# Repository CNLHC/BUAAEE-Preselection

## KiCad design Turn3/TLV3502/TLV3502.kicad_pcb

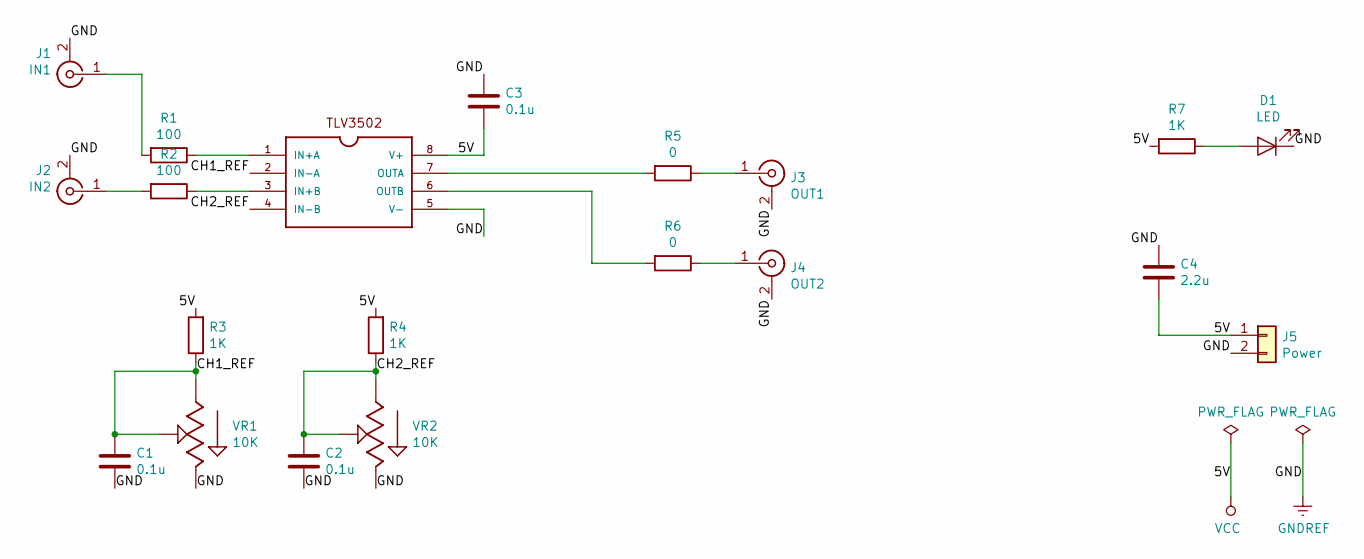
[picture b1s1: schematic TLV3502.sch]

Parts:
C1, C2, C3: 0.1u; C_0603_1608Metric_Pad1.05x0.95mm_HandSolder
C4: 2.2u; CP_EIA-3528-21_Kemet-B
D1: LED; LED_0805_2012Metric_Pad1.15x1.40mm_HandSolder
J1: IN1; SMA_Amphenol_132134_Vertical
J2: IN2; SMA_Amphenol_132134_Vertical
J3: OUT1; SMA_Amphenol_132134_Vertical
J4: OUT2; SMA_Amphenol_132134_Vertical
J5: Power; PinSocket_1x02_P2.54mm_Vertical
R1, R2: 100; R_0603_1608Metric_Pad1.05x0.95mm_HandSolder
R3, R4, R7: 1K; R_0603_1608Metric_Pad1.05x0.95mm_HandSolder
R5, R6: 0; R_0603_1608Metric_Pad1.05x0.95mm_HandSolder
U1: TLV3502; SOIC-8_3.9x4.9mm_P1.27mm
VR1, VR2: 10K; PinHeader_1x03_P2.54mm_Vertical

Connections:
/CH1_REF: C1.2, R3.1, U1.2 (IN-A), VR1.1 (CCW), VR1.2 (WIPER)
/CH2_REF: C2.2, R4.1, U1.4 (IN-B), VR2.1 (CCW), VR2.2 (WIPER)
GNDREF: C1.1, C2.1, C3.2, C4.2, D1.1 (K), J1.2 (Ext), J2.2 (Ext), J3.2 (Ext), J4.2 (Ext), J5.2, U1.5 (V-), VR1.3 (CW), VR2.3 (CW)
unnamed: D1.2 (A), R7.1
unnamed: J1.1 (In), R1.2
unnamed: J2.1 (In), R2.2
unnamed: J3.1 (In), R5.1
unnamed: J4.1 (In), R6.1
unnamed: R1.1, U1.1 (IN+A)
unnamed: R2.1, U1.3 (IN+B)
unnamed: R5.2, U1.7 (OUTA)
unnamed: R6.2, U1.6 (OUTB)
VCC: C3.1, C4.1, J5.1, R3.2, R4.2, R7.2, U1.8 (V+)

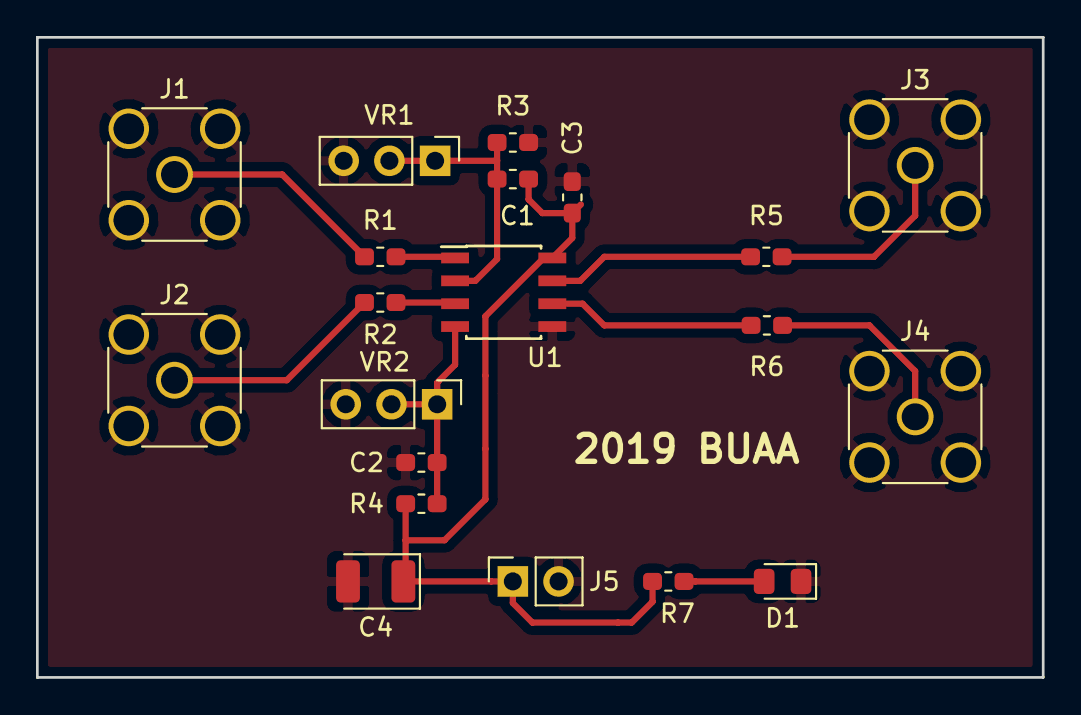
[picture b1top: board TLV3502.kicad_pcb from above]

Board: 2 copper layers, 55.9 x 35.6 mm, 20 parts (0 on the bottom side), 13 nets.

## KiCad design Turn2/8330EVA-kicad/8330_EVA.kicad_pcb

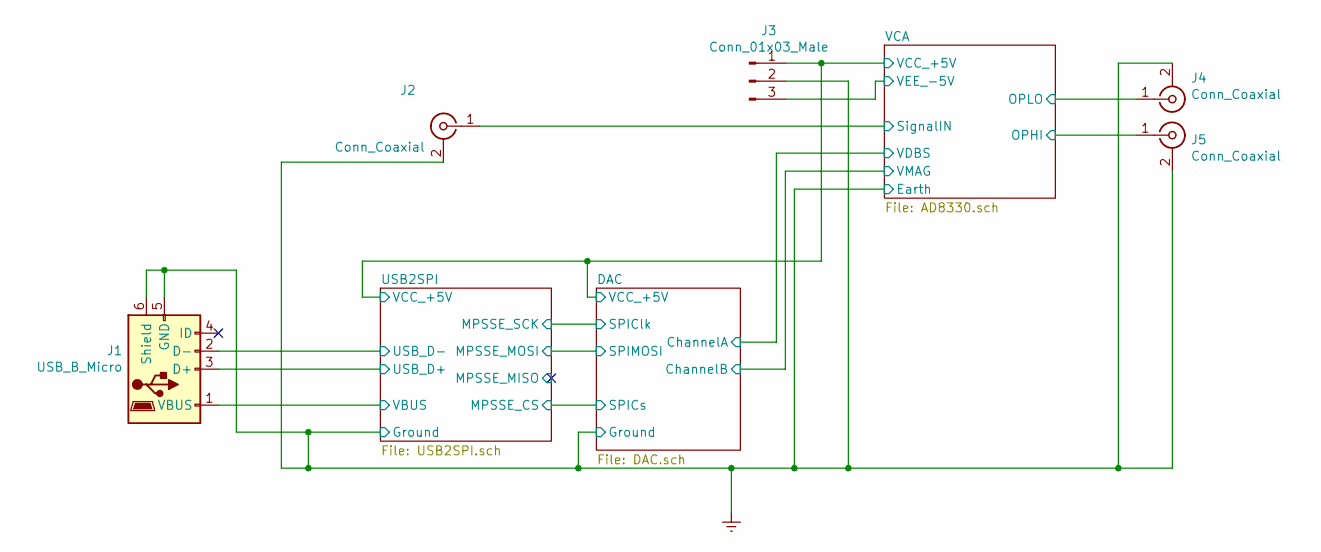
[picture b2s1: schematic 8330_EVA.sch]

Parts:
J1: USB_B_Micro; USB_Mini-B_Lumberg_2486_01_Horizontal
J2, J4, J5: Conn_Coaxial; SMA_Amphenol_132289_EdgeMount
J3: Conn_01x03_Male; PinHeader_1x03_P2.54mm_Vertical

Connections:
/DAC/VCC_+5V: J3.1; also elsewhere on the board
/USB2SPI/USB_D+: J1.3 (D+); also elsewhere on the board
/USB2SPI/USB_D-: J1.2 (D-); also elsewhere on the board
/USB2SPI/VBUS: J1.1 (VBUS); also elsewhere on the board
/VCA/OPHI: J5.1 (In); also elsewhere on the board
/VCA/OPLO: J4.1 (In); also elsewhere on the board
/VCA/SignalIN: J2.1 (In); also elsewhere on the board
/VCA/VEE_-5V: J3.3; also elsewhere on the board
Earth: J1.5 (GND), J1.6 (Shield), J2.2 (Ext), J3.2, J4.2 (Ext), J5.2 (Ext); also elsewhere on the board

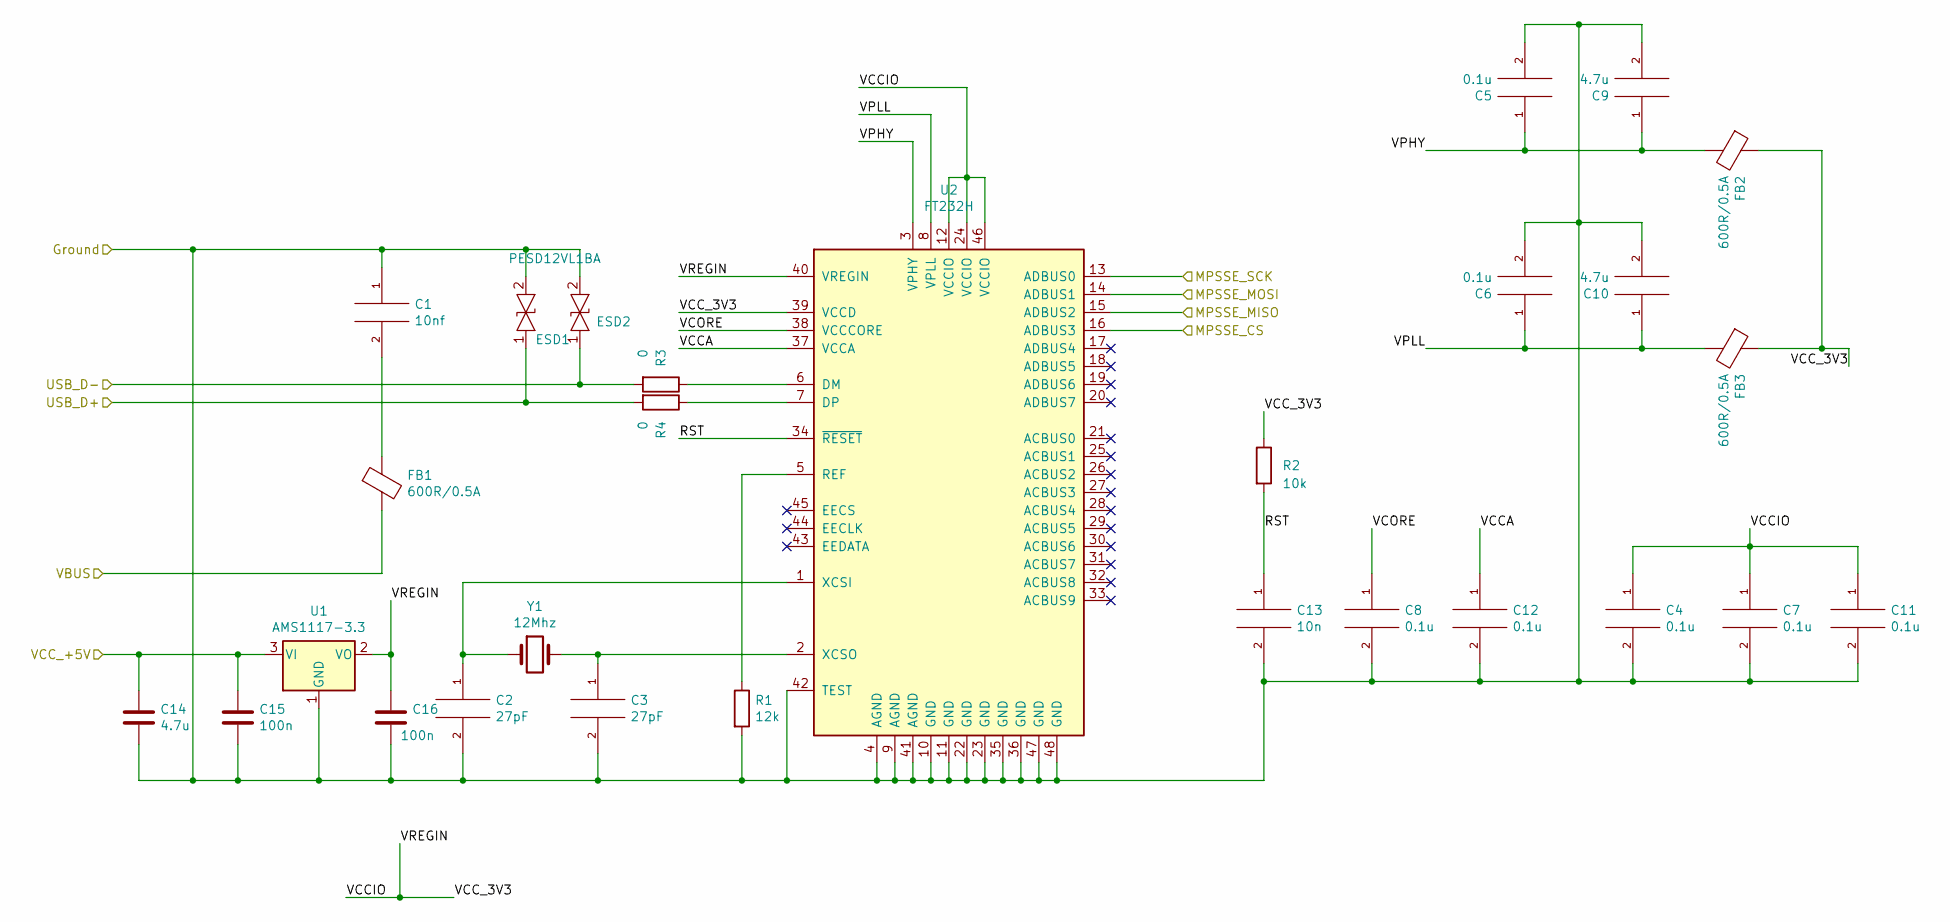
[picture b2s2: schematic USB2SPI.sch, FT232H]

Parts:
C1: 10nf; C_0603_1608Metric_Pad1.05x0.95mm_HandSolder
C2, C3: 27pF; C_0603_1608Metric_Pad1.05x0.95mm_HandSolder
C4, C5, C6, C7, C8, C11, C12: 0.1u; C_0603_1608Metric_Pad1.05x0.95mm_HandSolder
C9, C10, C14: 4.7u; C_0603_1608Metric_Pad1.05x0.95mm_HandSolder
C13: 10n; C_0603_1608Metric_Pad1.05x0.95mm_HandSolder
C15, C16: 100n; C_0603_1608Metric_Pad1.05x0.95mm_HandSolder
ESD1, ESD2: PESD12VL1BA; D_SOD-323_HandSoldering
FB1, FB2, FB3: 600R/0.5A; R_0805_2012Metric_Pad1.15x1.40mm_HandSolder
R1: 12k; R_0805_2012Metric_Pad1.15x1.40mm_HandSolder
R2: 10k; R_0805_2012Metric_Pad1.15x1.40mm_HandSolder
R3, R4: 0; R_0805_2012Metric_Pad1.15x1.40mm_HandSolder
U1: AMS1117-3.3; SOT-223-3_TabPin2
U2: FT232H; LQFP-48_7x7mm_P0.5mm
Y1: 12Mhz; Crystal_SMD_5032-2Pin_5.0x3.2mm_HandSoldering

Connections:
/DAC/VCC_+5V: C14.1, C15.1, U1.3 (VI); also elsewhere on the board
/USB2SPI/MPSSE_CS: U2.16 (ADBUS3); also elsewhere on the board
/USB2SPI/MPSSE_MISO: U2.15 (ADBUS2)
/USB2SPI/MPSSE_MOSI: U2.14 (ADBUS1); also elsewhere on the board
/USB2SPI/MPSSE_SCK: U2.13 (ADBUS0); also elsewhere on the board
/USB2SPI/RST: C13.1, R2.2, U2.34 (~RESET)
/USB2SPI/USB_D+: ESD1.1, R4.2; also elsewhere on the board
/USB2SPI/USB_D-: ESD2.1, R3.2; also elsewhere on the board
/USB2SPI/VBUS: FB1.2; also elsewhere on the board
/USB2SPI/VCCA: C12.1, U2.37 (VCCA)
/USB2SPI/VCCIO: C4.1, C7.1, C11.1, C16.1, FB2.1, FB3.1, R2.1, U1.2 (VO), U2.12 (VCCIO), U2.24 (VCCIO), U2.39 (VCCD), U2.40 (VREGIN), U2.46 (VCCIO)
/USB2SPI/VCORE: C8.1, U2.38 (VCCCORE)
/USB2SPI/VPHY: C5.1, C9.1, FB2.2, U2.3 (VPHY)
/USB2SPI/VPLL: C6.1, C10.1, FB3.2, U2.8 (VPLL)
Earth: C1.1, C2.2, C3.2, C4.2, C5.2, C6.2, C7.2, C8.2, C9.2, C10.2, C11.2, C12.2, C13.2, C14.2, C15.2, C16.2, ESD1.2, ESD2.2, R1.2, U1.1 (GND), U2.4 (AGND), U2.9 (AGND), U2.10 (GND), U2.11 (GND), U2.22 (GND), U2.23 (GND), U2.35 (GND), U2.36 (GND), U2.41 (AGND), U2.42 (TEST), U2.47 (GND), U2.48 (GND); also elsewhere on the board
unnamed: C1.2, FB1.1
unnamed: C2.1, U2.1 (XCSI), Y1.1
unnamed: C3.1, U2.2 (XCSO), Y1.2
unnamed: R1.1, U2.5 (REF)
unnamed: R3.1, U2.6 (DM)
unnamed: R4.1, U2.7 (DP)

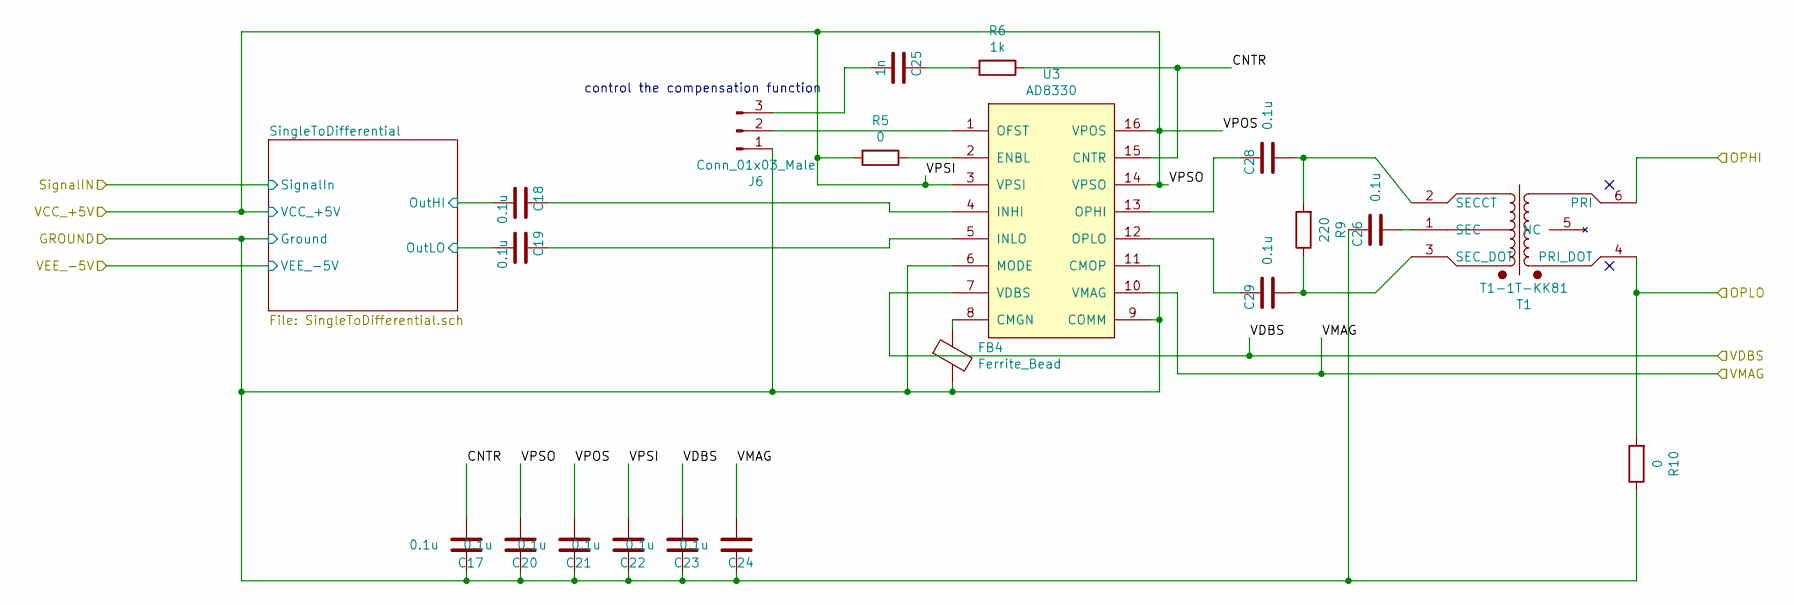
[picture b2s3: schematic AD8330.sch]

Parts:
C17, C18, C19, C20, C21, C22, C23, C24, C26, C28, C29: 0.1u; C_0603_1608Metric_Pad1.05x0.95mm_HandSolder
C25: 1n; C_0603_1608Metric_Pad1.05x0.95mm_HandSolder
FB4: Ferrite_Bead; L_0805_2012Metric_Pad1.15x1.40mm_HandSolder
J6: Conn_01x03_Male; PinHeader_1x03_P2.54mm_Vertical
R5, R10: 0; R_0805_2012Metric_Pad1.15x1.40mm_HandSolder
R6: 1k; R_0805_2012Metric_Pad1.15x1.40mm_HandSolder
R9: 220; R_0805_2012Metric_Pad1.15x1.40mm_HandSolder
T1: T1-1T-KK81; Mini_Circuit_RF_Transformer_SO6
U3: AD8330; QSOP-16_3.9x4.9mm_P0.635mm

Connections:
/DAC/ChannelA: C23.1, U3.7 (VDBS); also elsewhere on the board
/DAC/ChannelB: C24.1, U3.10 (VMAG); also elsewhere on the board
/DAC/VCC_+5V: C20.1, C21.1, C22.1, R5.2, U3.3 (VPSI), U3.14 (VPSO), U3.16 (VPOS); also elsewhere on the board
/VCA/CNTR: C17.1, R6.1, U3.15 (CNTR)
/VCA/OPHI: T1.6 (PRI); also elsewhere on the board
/VCA/OPLO: R10.2, T1.4 (PRI_DOT); also elsewhere on the board
/VCA/SingleToDifferential/OutHI: C18.1; also elsewhere on the board
/VCA/SingleToDifferential/OutLO: C19.1; also elsewhere on the board
Earth: C17.2, C20.2, C21.2, C22.2, C23.2, C24.2, C26.2, FB4.2, J6.1, R10.1, U3.6 (MODE), U3.9 (COMM), U3.11 (CMOP); also elsewhere on the board
unnamed: C18.2, U3.4 (INHI)
unnamed: C19.2, U3.5 (INLO)
unnamed: C25.1, J6.3
unnamed: C25.2, R6.2
unnamed: C26.1, T1.1 (SEC)
unnamed: C28.1, R9.2, T1.2 (SECCT)
unnamed: C28.2, U3.13 (OPHI)
unnamed: C29.1, R9.1, T1.3 (SEC_DOT)
unnamed: C29.2, U3.12 (OPLO)
unnamed: FB4.1, U3.8 (CMGN)
unnamed: J6.2, U3.1 (OFST)
unnamed: R5.1, U3.2 (ENBL)

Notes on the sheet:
control the compensation function

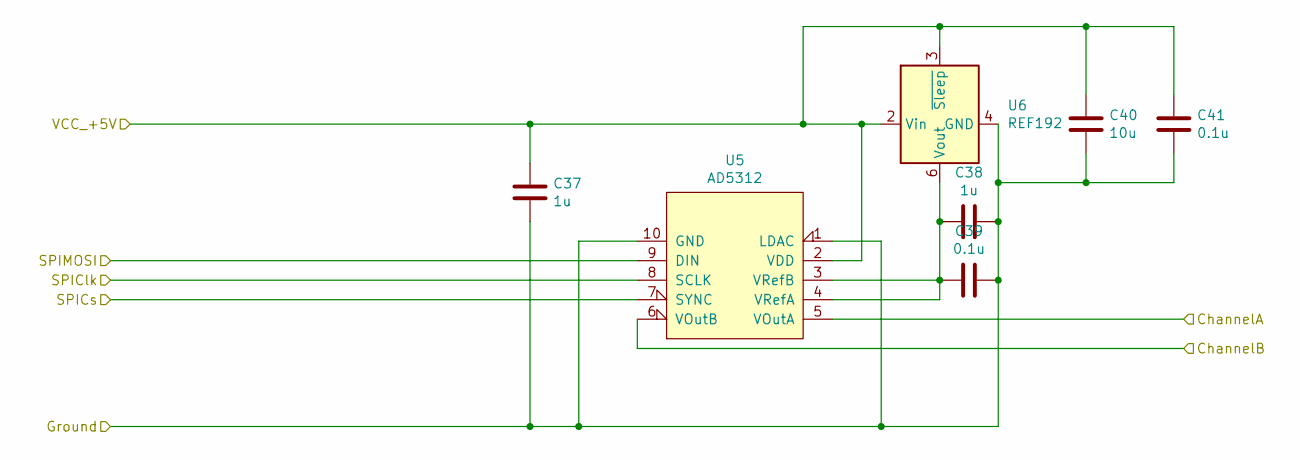
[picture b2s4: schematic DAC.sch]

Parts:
C37, C38: 1u; C_0603_1608Metric_Pad1.05x0.95mm_HandSolder
C39, C41: 0.1u; C_0603_1608Metric_Pad1.05x0.95mm_HandSolder
C40: 10u; C_0603_1608Metric_Pad1.05x0.95mm_HandSolder
U5: AD5312; MSOP-10_3x3mm_P0.5mm
U6: REF192; SOIC-8_3.9x4.9mm_P1.27mm

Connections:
/DAC/ChannelA: U5.5 (VOutA); also elsewhere on the board
/DAC/ChannelB: U5.6 (VOutB); also elsewhere on the board
/DAC/VCC_+5V: C37.1, C40.1, C41.1, U5.2 (VDD), U6.2 (Vin), U6.3 (~Sleep~); also elsewhere on the board
/USB2SPI/MPSSE_CS: U5.7 (SYNC); also elsewhere on the board
/USB2SPI/MPSSE_MOSI: U5.9 (DIN); also elsewhere on the board
/USB2SPI/MPSSE_SCK: U5.8 (SCLK); also elsewhere on the board
Earth: C37.2, C38.1, C39.1, C40.2, C41.2, U5.1 (LDAC), U5.10 (GND), U6.4 (GND); also elsewhere on the board
unnamed: C38.2, C39.2, U5.3 (VRefB), U5.4 (VRefA), U6.6 (Vout)

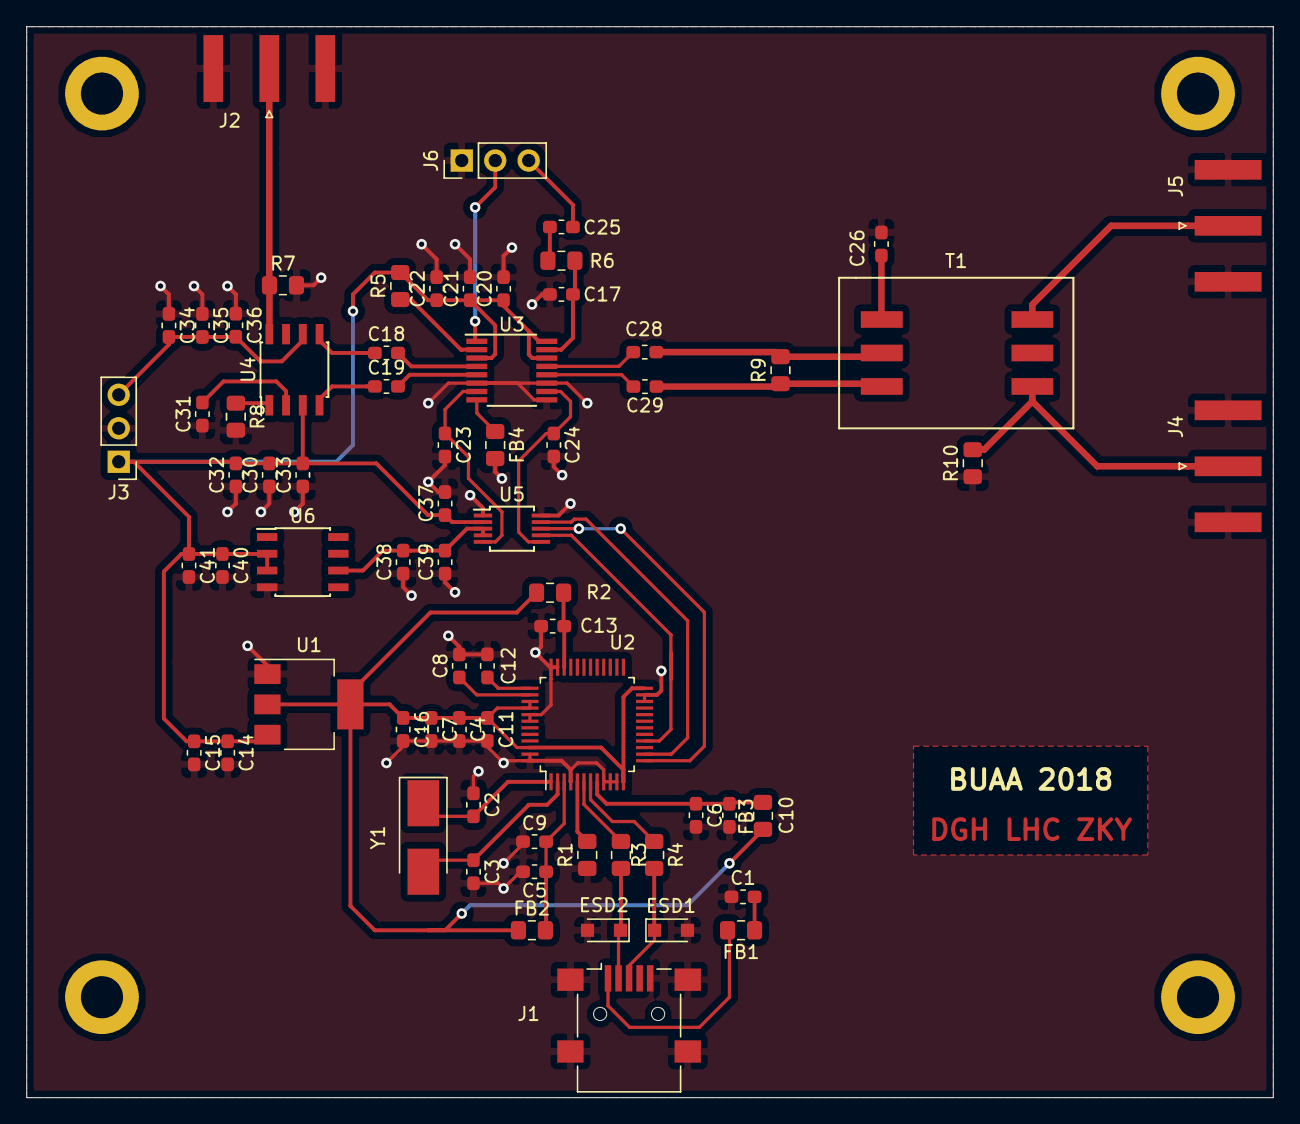
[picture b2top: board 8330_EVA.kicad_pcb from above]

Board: 2 copper layers, 94.6 x 81.3 mm, 70 parts (0 on the bottom side), 44 nets.

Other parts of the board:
C30, C31, C34: 0.1u; C_0603_1608Metric_Pad1.05x0.95mm_HandSolder
C32, C35: 10u; C_0603_1608Metric_Pad1.05x0.95mm_HandSolder
C33, C36: 10n; C_0603_1608Metric_Pad1.05x0.95mm_HandSolder
R7: 49.9; R_0805_2012Metric_Pad1.15x1.40mm_HandSolder
R8: 24.9; R_0805_2012Metric_Pad1.15x1.40mm_HandSolder
U4: AD8131; SOIC-8_3.9x4.9mm_P1.27mm

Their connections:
/DAC/VCC_+5V: C30.2, C32.2, C33.2, U4.3; also elsewhere on the board
/VCA/SignalIN: R7.1, U4.8; also elsewhere on the board
/VCA/SingleToDifferential/OutHI: U4.5; also elsewhere on the board
/VCA/SingleToDifferential/OutLO: U4.4; also elsewhere on the board
/VCA/VEE_-5V: C34.2, C35.2, C36.2, U4.6; also elsewhere on the board
Earth: C30.1, C31.1, C32.1, C33.1, C34.1, C35.1, C36.1, R7.2, R8.2; also elsewhere on the board
unnamed: C31.2, U4.2
unnamed: R8.1, U4.1

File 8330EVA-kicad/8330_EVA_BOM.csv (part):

"Source:","C:\Users\cn\Desktop\Project\BUAAEE-Preselection1\8330EVA-kicad\8330_EVA.sch"
"Date:","2018/11/27 8:59:51"
"Tool:","Eeschema (6.0.0-rc1-dev-1154-gcbd13c712)"
"Generator:","C:\Program Files\KiCad\bin\scripting\plugins/bom_csv_grouped_by_value.py"
"Component Count:","70"

"Individual Components:"

"Item","Qty","Reference(s)","Value","LibPart","Footprint","Datasheet"
"","","C1","10nf","pspice:CAP","Capacitor_SMD:C_0603_1608Metric_Pad1.05x0.95mm_HandSolder","~"
"","","C2","27pF","pspice:CAP","Capacitor_SMD:C_0603_1608Metric_Pad1.05x0.95mm_HandSolder","~"
"","","C3","27pF","pspice:CAP","Capacitor_SMD:C_0603_1608Metric_Pad1.05x0.95mm_HandSolder","~"
"","","C4","0.1u","pspice:CAP","Capacitor_SMD:C_0603_1608Metric_Pad1.05x0.95mm_HandSolder","~"
"","","C5","0.1u","pspice:CAP","Capacitor_SMD:C_0603_1608Metric_Pad1.05x0.95mm_HandSolder","~"
"","","C6","0.1u","pspice:CAP","Capacitor_SMD:C_0603_1608Metric_Pad1.05x0.95mm_HandSolder","~"
"","","C7","0.1u","pspice:CAP","Capacitor_SMD:C_0603_1608Metric_Pad1.05x0.95mm_HandSolder","~"
"","","C8","0.1u","pspice:CAP","Capacitor_SMD:C_0603_1608Metric_Pad1.05x0.95mm_HandSolder","~"
"","","C9","4.7u","pspice:CAP","Capacitor_SMD:C_0603_1608Metric_Pad1.05x0.95mm_HandSolder","~"
"","","C10","4.7u","pspice:CAP","Capacitor_SMD:C_0603_1608Metric_Pad1.05x0.95mm_HandSolder","~"
"","","C11","0.1u","pspice:CAP","Capacitor_SMD:C_0603_1608Metric_Pad1.05x0.95mm_HandSolder","~"
"","","C12","0.1u","pspice:CAP","Capacitor_SMD:C_0603_1608Metric_Pad1.05x0.95mm_HandSolder","~"
"","","C13","10n","pspice:CAP","Capacitor_SMD:C_0603_1608Metric_Pad1.05x0.95mm_HandSolder","~"
"","","C14","4.7u","Device:C","Capacitor_SMD:C_0603_1608Metric_Pad1.05x0.95mm_HandSolder","~"
"","","C15","100n","Device:C","Capacitor_SMD:C_0603_1608Metric_Pad1.05x0.95mm_HandSolder","~"
"","","C16","100n","Device:C","Capacitor_SMD:C_0603_1608Metric_Pad1.05x0.95mm_HandSolder","~"
"","","C17","0.1u","Device:C","Capacitor_SMD:C_0603_1608Metric_Pad1.05x0.95mm_HandSolder","~"
"","","C18","0.1u","Device:C","Capacitor_SMD:C_0603_1608Metric_Pad1.05x0.95mm_HandSolder","~"
"","","C19","0.1u","Device:C","Capacitor_SMD:C_0603_1608Metric_Pad1.05x0.95mm_HandSolder","~"
"","","C20","0.1u","Device:C","Capacitor_SMD:C_0603_1608Metric_Pad1.05x0.95mm_HandSolder","~"
"","","C21","0.1u","Device:C","Capacitor_SMD:C_0603_1608Metric_Pad1.05x0.95mm_HandSolder","~"
"","","C22","0.1u","Device:C","Capacitor_SMD:C_0603_1608Metric_Pad1.05x0.95mm_HandSolder","~"
"","","C23","0.1u","Device:C","Capacitor_SMD:C_0603_1608Metric_Pad1.05x0.95mm_HandSolder","~"
"","","C24","0.1u","Device:C","Capacitor_SMD:C_0603_1608Metric_Pad1.05x0.95mm_HandSolder","~"
"","","C25","1n","Device:C","Capacitor_SMD:C_0603_1608Metric_Pad1.05x0.95mm_HandSolder","~"
"","","C26","12p","Device:C","Capacitor_SMD:C_0603_1608Metric_Pad1.05x0.95mm_HandSolder","~"
"","","C27","12p","Device:C","Capacitor_SMD:C_0603_1608Metric_Pad1.05x0.95mm_HandSolder","~"
"","","C28","0.1u","Device:C","Capacitor_SMD:C_0603_1608Metric_Pad1.05x0.95mm_HandSolder","~"
"","","C29","0.1u","Device:C","Capacitor_SMD:C_0603_1608Metric_Pad1.05x0.95mm_HandSolder","~"
"","","C30","0.1u","Device:C","Capacitor_SMD:C_0603_1608Metric_Pad1.05x0.95mm_HandSolder","~"
"","","C31","0.1u","Device:C","Capacitor_SMD:C_0603_1608Metric_Pad1.05x0.95mm_HandSolder","~"
"","","C32","10u","Device:C","Capacitor_SMD:C_0603_1608Metric_Pad1.05x0.95mm_HandSolder","~"
"","","C33","10n","Device:C","Capacitor_SMD:C_0603_1608Metric_Pad1.05x0.95mm_HandSolder","~"
"","","C34","0.1u","Device:C","Capacitor_SMD:C_0603_1608Metric_Pad1.05x0.95mm_HandSolder","~"
"","","C35","10u","Device:C","Capacitor_SMD:C_0603_1608Metric_Pad1.05x0.95mm_HandSolder","~"
"","","C36","10n","Device:C","Capacitor_SMD:C_0603_1608Metric_Pad1.05x0.95mm_HandSolder","~"
"","","C37","1u","Device:C","Capacitor_SMD:C_0603_1608Metric_Pad1.05x0.95mm_HandSolder","~"
"","","C38","1u","Device:C","Capacitor_SMD:C_0603_1608Metric_Pad1.05x0.95mm_HandSolder","~"
"","","C39","0.1u","Device:C","Capacitor_SMD:C_0603_1608Metric_Pad1.05x0.95mm_HandSolder","~"
"","","C40","10u","Device:C","Capacitor_SMD:C_0603_1608Metric_Pad1.05x0.95mm_HandSolder","~"
"","","C41","0.1u","Device:C","Capacitor_SMD:C_0603_1608Metric_Pad1.05x0.95mm_HandSolder","~"
"","","ESD1","PESD12VL1BA","8330_EVA-extra:PESD12VL1BA","Diode_SMD:D_SOD-323_HandSoldering",""
"","","ESD2","PESD12VL1BA","8330_EVA-extra:PESD12VL1BA","Diode_SMD:D_SOD-323_HandSoldering",""
"","","FB1","600R/0.5A","Device:Ferrite_Bead","Resistor_SMD:R_0805_2012Metric_Pad1.15x1.40mm_HandSolder","~"
"","","FB2","600R/0.5A","Device:Ferrite_Bead","Resistor_SMD:R_0805_2012Metric_Pad1.15x1.40mm_HandSolder","~"
"","","FB3","600R/0.5A","Device:Ferrite_Bead","Resistor_SMD:R_0805_2012Metric_Pad1.15x1.40mm_HandSolder","~"
"","","FB4","Ferrite_Bead","Device:Ferrite_Bead","Inductor_SMD:L_0805_2012Metric_Pad1.15x1.40mm_HandSolder","~"
"","","J1","USB_B_Micro","Connector:USB_B_Micro","Connector_USB:USB_Mini-B_Lumberg_2486_01_Horizontal","~"
"","","J2","Conn_Coaxial","Connector:Conn_Coaxial","Connector_Coaxial:SMA_Amphenol_132289_EdgeMount"," ~"
"","","J3","Conn_01x03_Male","Connector:Conn_01x03_Male","Connector_PinHeader_2.54mm:PinHeader_1x03_P2.54mm_Vertical","~"
"","","J4","Conn_Coaxial","Connector:Conn_Coaxial","Connector_Coaxial:SMA_Amphenol_132289_EdgeMount"," ~"
"","","J5","Conn_Coaxial","Connector:Conn_Coaxial","Connector_Coaxial:SMA_Amphenol_132289_EdgeMount"," ~"
"","","J6","Conn_01x03_Male","Connector:Conn_01x03_Male","Connector_PinHeader_2.54mm:PinHeader_1x03_P2.54mm_Vertical","~"
"","","R1","12k","Device:R","Resistor_SMD:R_0805_2012Metric_Pad1.15x1.40mm_HandSolder","~"
"","","R2","10k","Device:R","Resistor_SMD:R_0805_2012Metric_Pad1.15x1.40mm_HandSolder","~"
"","","R3","0","Device:R","Resistor_SMD:R_0805_2012Metric_Pad1.15x1.40mm_HandSolder","~"
"","","R4","0","Device:R","Resistor_SMD:R_0805_2012Metric_Pad1.15x1.40mm_HandSolder","~"
"","","R5","0","Device:R","Resistor_SMD:R_0805_2012Metric_Pad1.15x1.40mm_HandSolder","~"
"","","R6","1k","Device:R","Resistor_SMD:R_0805_2012Metric_Pad1.15x1.40mm_HandSolder","~"
"","","R7","49.9","Device:R","Resistor_SMD:R_0805_2012Metric_Pad1.15x1.40mm_HandSolder","~"
"","","R8","24.9","Device:R","Resistor_SMD:R_0805_2012Metric_Pad1.15x1.40mm_HandSolder","~"
"","","T1","T1-1T-KK81","8330_EVA-extra:T1-1T-KK81","8330EVA-footprint-extra:Mini_Circuit_RF_Transformer_SO6","https://ww3.minicircuits.com/pdfs/T1-1T-KK81.pdf"
"","","T2","T1-1T-KK81","8330_EVA-extra:T1-1T-KK81","8330EVA-footprint-extra:Mini_Circuit_RF_Transformer_SO6","https://ww3.minicircuits.com/pdfs/T1-1T-KK81.pdf"
"","","U1","AMS1117-3.3","Regulator_Linear:AMS1117-3.3","Package_TO_SOT_SMD:SOT-223-3_TabPin2","http://www.advanced-monolithic.com/pdf/ds1117.pdf"
"","","U2","FT232H","Interface_USB:FT232H","Package_QFP:LQFP-48_7x7mm_P0.5mm","http://www.ftdichip.com/Products/ICs/FT232H.htm"
"","","U3","AD8330","8330_EVA-extra:AD8330","Package_SO:QSOP-16_3.9x4.9mm_P0.635mm","https://www.analog.com/media/en/technical-documentation/data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"
"","","U4","AD8131","8330_EVA-extra:AD8131","Package_SO:SOIC-8_3.9x4.9mm_P1.27mm","https://www.analog.com/media/en/technical-documentation/data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"
"","","U5","AD5312","8330_EVA-extra:AD5312","Package_SO:MSOP-10_3x3mm_P0.5mm",""
"","","U6","REF192","Reference_Voltage:REF192","Package_SO:SOIC-8_3.9x4.9mm_P1.27mm","http://www.analog.com/static/imported-files/data_sheets/REF1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"
"","","Y1","12Mhz","Device:Crystal","Crystal:Crystal_SMD_5032-2Pin_5.0x3.2mm_HandSoldering","~"



"Collated Components:"

"Item","Qty","Reference(s)","Value","LibPart","Footprint","Datasheet"
"1","1","C1","10nf","pspice:CAP","Capacitor_SMD:C_0603_1608Metric_Pad1.05x0.95mm_HandSolder","~"
"2","2","C2, C3","27pF","pspice:CAP","Capacitor_SMD:C_0603_1608Metric_Pad1.05x0.95mm_HandSolder","~"
"3","7","C4, C5, C6, C7, C8, C11, C12","0.1u","pspice:CAP","Capacitor_SMD:C_0603_1608Metric_Pad1.05x0.95mm_HandSolder","~"
"4","2","C9, C10","4.7u","pspice:CAP","Capacitor_SMD:C_0603_1608Metric_Pad1.05x0.95mm_HandSolder","~"
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
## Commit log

2018-11-16 first-commit
2018-11-16 完成FT232驱动电路原理图的绘制，并未相关的元件添加了封装
2018-11-16 整理封装库，添加DAC AD5312封装
2018-11-23 add symbol/package of AD8131 and AD8330
2018-11-23 添加射频变压器T1-1T-KK81符号
2018-11-24 完成AD8131单端转差分放大原理图绘制
2018-11-24 对齐变压器的网格
2018-11-24 绘制了变压器同名端，修复了引脚标识的错误
2018-11-24 完成AD8330 VGA电路原理图的绘制
2018-11-24 添加DAC部分/修改FT232供电方式（原理图）
    1. 完成AD5312及REF192组成的程控信号产生部分原理图绘制
    2. 修改FT232H的供电方式，添加了3.3VLDO，从之前的BUS-Power改为Self_Power
2018-11-24 修复若干ERC未连接错误
2018-11-24 修复FT232 Test脚链接错误
2018-11-24 为变压器制作封装
2018-11-24 修复AD8330模块中的错误
    1. VCC连接错误
    2. VPOS和VPSO标反
2018-11-25 完成变压器3d模型绘制
2018-11-25 更新3d模型，替换SMA接头的封装
2018-11-26 Finished PCB layout, connect Earth to Ground
2018-11-27 简单修改
    1. 修改了差分输出处的布线，提高对称性
    2. 修改了USB接口的封装。现在使用完全表面贴装的Mini USB接口
    3. 在电路板上添加了要求的信息
    4. 生成了BOM表和Gerber文件
2018-11-27 添加M3安装孔，调整SMA焊盘位置
2018-11-28 改变巴伦的使用方式
2018-11-28 生成gerber文件
2018-11-28 重新生成BOM表
2018-11-28 生成坐标文件，并手动删除不需要厂家贴装的元件
2018-11-28 生成嘉利创要求的BOM表和POS文件
2019-03-16 整理目录
    添加第三次选拔工程文件
2019-03-16 添加TLV3502高速比较器评估版硬件设计
2019-03-17 添加频率测量实现
2019-03-17 添加鉴相器
2019-03-17 添加超高速时钟生成模块
2019-03-17 向Quartus项目中添加工程文件。完成FrequencyMeter Qsys的搭建
2019-03-17 添加verilator目录设置
2019-03-17 在顶层模块中引出自定义频率测量模块的引脚
2019-03-17 修复部分字宽的问题。完成核心模块的实例化。
2019-03-25 联合调试前更新
2019-05-11 添加9910驱动
2019-05-19 完成AD9910驱动
2019-05-19 完成ADC7606驱动
2019-05-19 完成DAC8563驱动
2019-05-19 添加D2xx bitmode 操作快捷方式
2019-05-19 整理目录
2019-05-19 添加主文件
2019-05-19 建立CubeMX工程文件
2019-05-19 完成帧同步逻辑
2019-05-19 整理keil目录
2019-05-21 添加扫频函数
